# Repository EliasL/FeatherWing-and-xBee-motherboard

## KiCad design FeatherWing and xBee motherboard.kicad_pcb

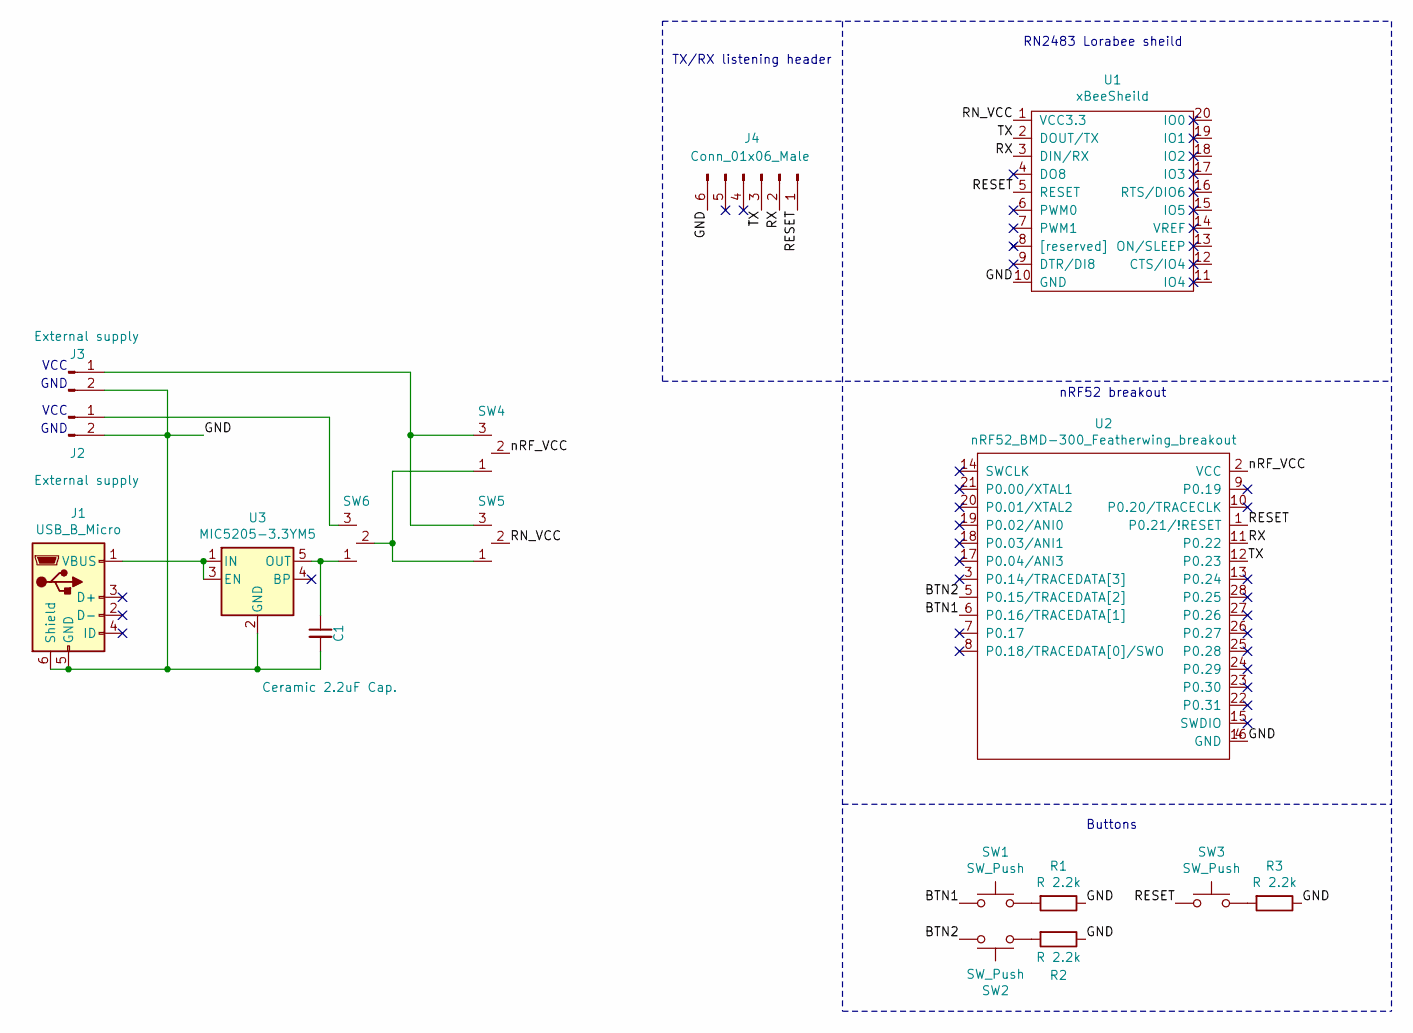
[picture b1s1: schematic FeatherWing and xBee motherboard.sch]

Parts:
C1: Ceramic 2.2uF Cap.; C_0603_1608Metric_Pad1.05x0.95mm_HandSolder
J1: USB_B_Micro; USB_Micro-B_Molex_47346-0001
J2, J3: External supply; PinHeader_1x02_P2.54mm_Vertical_SMD_Pin1Left
J4: Conn_01x06_Male; PinSocket_1x06_P2.54mm_Vertical_SMD_Pin1Right
R1, R2, R3: R 2.2k; R_0603_1608Metric_Pad1.05x0.95mm_HandSolder
SW1, SW2, SW3: SW_Push; MC32882 tactile switch SMD MCDTSZML-6 Series
SW4, SW5, SW6: HeaderSwitch; PinHeader_1x03_P2.54mm_Vertical_SMD_Pin1Left
U1: xBeeSheild; XBEE_PRO-20_THT_SMD_Socket
U2: nRF52_BMD-300_Featherwing_breakout; PCB_FeatherWing_SMD_Socket
U3: MIC5205-3.3YM5; 5-Lead SOT-23

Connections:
/BTN1: SW1.1, U2.6 (P0.16/TRACEDATA[1])
/BTN2: SW2.2, U2.5 (P0.15/TRACEDATA[2])
/GND: C1.2, J1.5 (GND), J1.6 (Shield), J2.2, J3.2, J4.6, R1.1, R2.1, R3.1, U1.10 (GND), U2.4 (GND), U2.16 (GND), U3.2 (GND)
/RESET: J4.1, SW3.1, U1.5 (RESET), U2.1 (P0.21/!RESET)
/RN_VCC: SW5.2 (out), U1.1 (VCC3.3)
/RX: J4.2, U1.3 (DIN/RX), U2.11 (P0.22)
/TX: J4.3, U1.2 (DOUT/TX), U2.12 (P0.23)
/nRF_VCC: SW4.2 (out), U2.2 (VCC)
unnamed: C1.1, SW6.1 (in1), U3.5 (OUT)
unnamed: J1.1 (VBUS), U3.1 (IN), U3.3 (EN)
unnamed: J2.1, SW6.3 (in2)
unnamed: J3.1, SW4.3 (in2), SW5.3 (in2)
unnamed: R1.2, SW1.2
unnamed: R2.2, SW2.1
unnamed: R3.2, SW3.2
unnamed: SW4.1 (in1), SW5.1 (in1), SW6.2 (out)

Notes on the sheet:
nRF52 breakout
RN2483 Lorabee sheild
VCC
GND
Buttons
TX/RX listening header

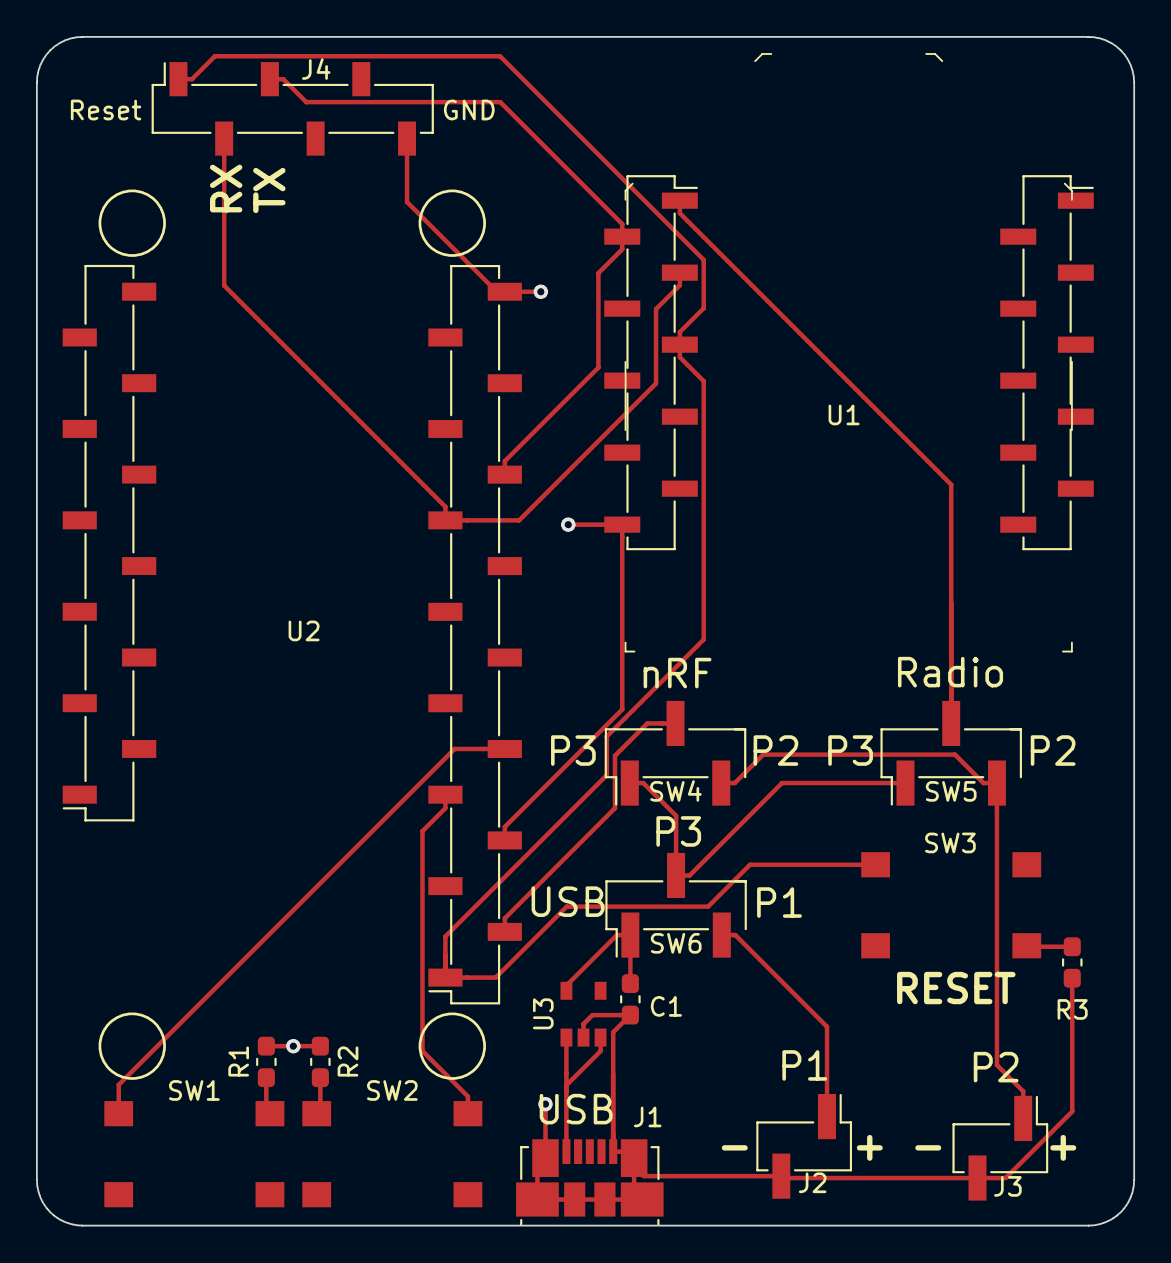
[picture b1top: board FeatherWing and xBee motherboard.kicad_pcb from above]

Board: 2 copper layers, 61.0 x 66.0 mm, 17 parts (0 on the bottom side), 16 nets.

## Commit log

2019-04-03 Init commit
2019-04-03 Moved text
2019-04-03 New image
